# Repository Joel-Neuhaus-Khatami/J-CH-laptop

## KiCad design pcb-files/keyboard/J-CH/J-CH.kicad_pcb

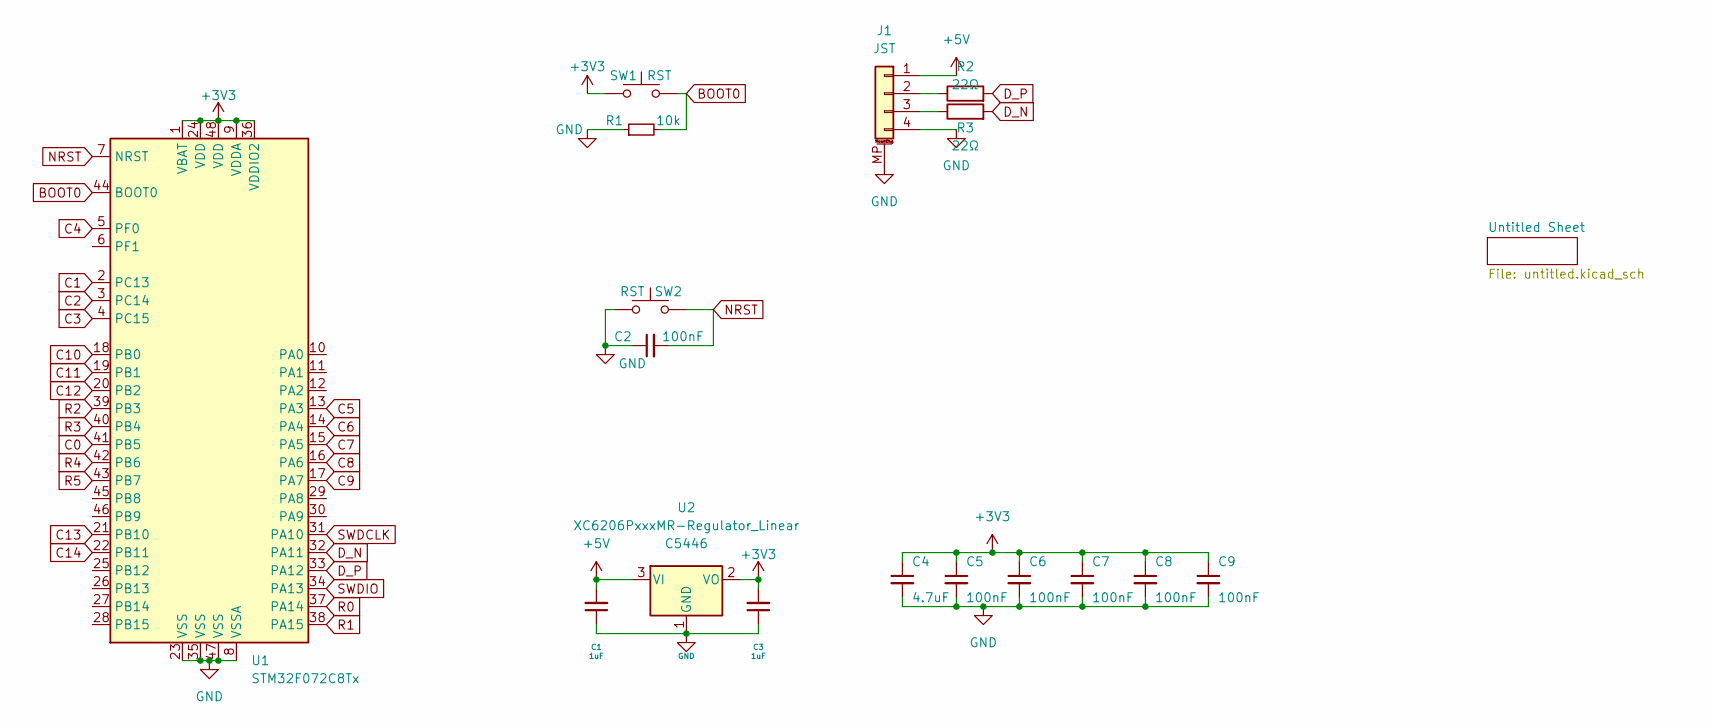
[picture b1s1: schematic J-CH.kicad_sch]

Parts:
C1, C3: 1uF; C_0402_1005Metric; LCSC C52923
C2, C5, C6, C7, C8, C9: 100nF; C_0402_1005Metric; LCSC C307331
C4: 4.7uF; C_0402_1005Metric; LCSC C23733
J1: JST; Molex_Pico-EZmate_78171-0004_1x04-1MP_P1.20mm_Vertical; LCSC C588524
R1: 10k; R_0402_1005Metric; LCSC C25744
R2, R3: 22Ω; C_0402_1005Metric; LCSC C25092
SW1, SW2: RST; SW_SPST_SKQG_WithoutStem; LCSC C139779
U1: STM32F072C8Tx; LQFP-48_7x7mm_P0.5mm; LCSC C80488
U2: XC6206PxxxMR-Regulator_Linear; SOT-23; LCSC C5446

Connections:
+3V3: C3.2, C4.1, C5.1, C6.1, C7.1, C8.1, C9.1, SW1.1, U1.1 (VBAT), U1.9 (VDDA), U1.24 (VDD), U1.36 (VDDIO2), U1.48 (VDD), U2.2 (VO)
+5V: C1.2, J1.1, U2.3 (VI)
BOOT0: R1.2, SW1.2, U1.44 (BOOT0)
C0: U1.41 (PB5); also elsewhere on the board
C1: U1.2 (PC13); also elsewhere on the board
C2: U1.3 (PC14); also elsewhere on the board
C3: U1.4 (PC15); also elsewhere on the board
C4: U1.5 (PF0); also elsewhere on the board
C5: U1.13 (PA3); also elsewhere on the board
C6: U1.14 (PA4); also elsewhere on the board
C7: U1.15 (PA5); also elsewhere on the board
C8: U1.16 (PA6); also elsewhere on the board
C9: U1.17 (PA7); also elsewhere on the board
C10: U1.18 (PB0); also elsewhere on the board
C11: U1.19 (PB1); also elsewhere on the board
C12: U1.20 (PB2); also elsewhere on the board
C13: U1.21 (PB10); also elsewhere on the board
C14: U1.22 (PB11); also elsewhere on the board
D_N: R2.2, U1.32 (PA11)
D_P: R3.2, U1.33 (PA12)
GND: C1.1, C2.1, C3.1, C4.2, C5.2, C6.2, C7.2, C8.2, C9.2, J1.4, J1.MP (MountPin), R1.1, SW2.2, U1.8 (VSSA), U1.23 (VSS), U1.35 (VSS), U1.47 (VSS), U2.1 (GND); also elsewhere on the board
NRST: C2.2, SW2.1, U1.7 (NRST); also elsewhere on the board
unnamed: J1.2, R3.1
unnamed: J1.3, R2.1
R0: U1.37 (PA14); also elsewhere on the board
R1: U1.38 (PA15); also elsewhere on the board
R2: U1.39 (PB3); also elsewhere on the board
R3: U1.40 (PB4); also elsewhere on the board
R4: U1.42 (PB6); also elsewhere on the board
R5: U1.43 (PB7); also elsewhere on the board
SWDCLK: U1.31 (PA10)
SWDIO: U1.34 (PA13)

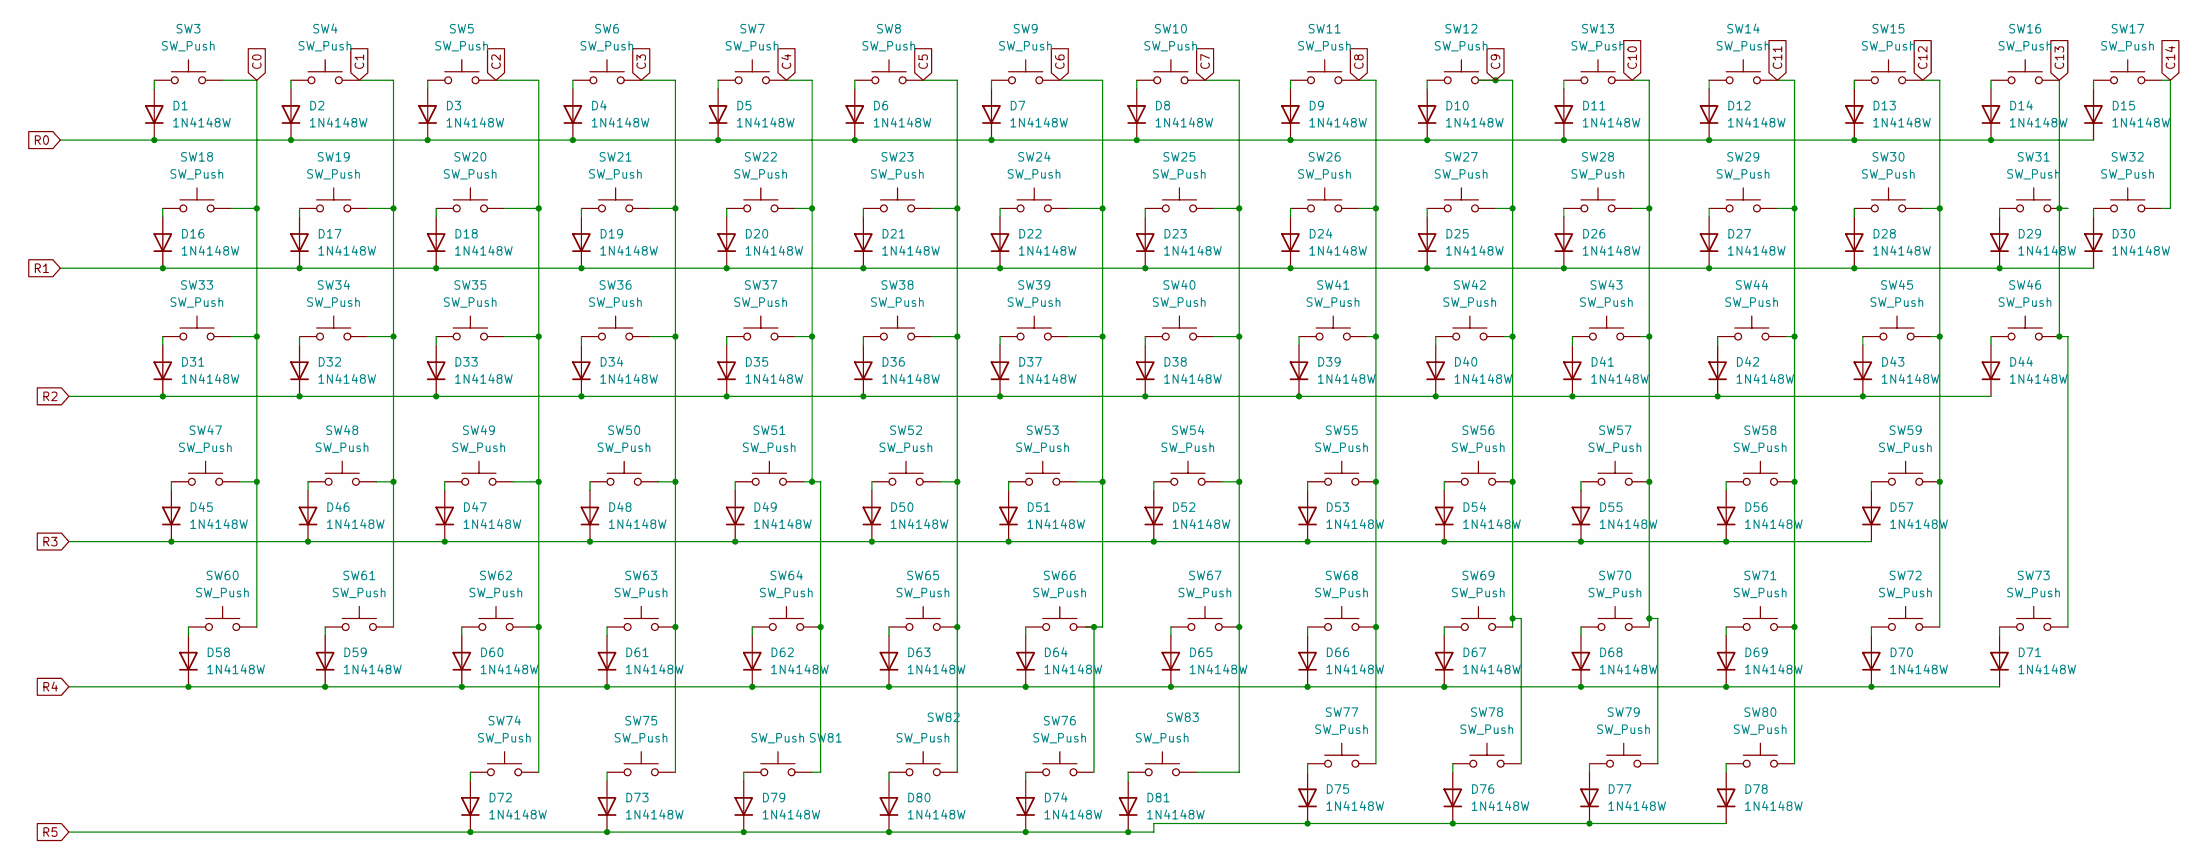
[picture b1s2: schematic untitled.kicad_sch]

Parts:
D1, D2, D3, D4, D5, D6, D7, D8, D9, D10, D11, D12, D13, D14, D15, D16, D17, D18, D19, D20, D21, D22, D23, D24, D25, D26, D27, D28, D29, D30, D31, D32, D33, D34, D35, D36, D37, D38, D39, D40, D41, D42, D43, D44, D45, D46, D47, D48, D49, D50, D51, D52, D53, D54, D55, D56, D57, D58, D59, D60, D61, D62, D63, D64, D65, D66, D67, D68, D69, D70, D71, D72, D73, D74, D75, D76, D77, D78, D79, D80, D81: 1N4148W; D_SOD-123
SW3, SW4, SW5, SW6, SW7, SW8, SW9, SW10, SW11, SW12, SW13, SW14, SW15, SW16, SW17, SW18, SW19, SW20, SW21, SW22, SW23, SW24, SW25, SW26, SW27, SW28, SW29, SW30, SW31, SW32, SW34, SW35, SW36, SW37, SW38, SW39, SW40, SW41, SW42, SW43, SW44, SW45, SW48, SW49, SW50, SW51, SW52, SW53, SW54, SW55, SW56, SW57, SW58, SW61, SW62, SW63, SW64, SW65, SW66, SW67, SW68, SW69, SW70, SW71, SW73, SW75, SW77, SW78, SW79, SW80, SW82: SW_Push; SW_Cherry_MX_1.00u_PCB
SW33, SW46, SW81, SW83: SW_Push; SW_Cherry_MX_1.50u_PCB
SW47, SW72: SW_Push; SW_Cherry_MX_1.75u_PCB
SW59: SW_Push; SW_Cherry_MX_2.25u_PCB
SW60, SW74: SW_Push; SW_Cherry_MX_1.25u_PCB
SW76: SW_Push; SW_Cherry_MX_6.25u_PCB

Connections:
C0: SW3.2, SW18.2, SW33.2, SW47.2, SW60.2; also elsewhere on the board
C1: SW4.2, SW19.2, SW34.2, SW48.2, SW61.2; also elsewhere on the board
C2: SW5.2, SW20.2, SW35.2, SW49.2, SW62.2, SW74.2; also elsewhere on the board
C3: SW6.2, SW21.2, SW36.2, SW50.2, SW63.2, SW75.2; also elsewhere on the board
C4: SW7.2, SW22.2, SW37.2, SW51.2, SW64.2, SW81.2; also elsewhere on the board
C5: SW8.2, SW23.2, SW38.2, SW52.2, SW65.2, SW82.2; also elsewhere on the board
C6: SW9.2, SW24.2, SW39.2, SW53.2, SW66.2, SW76.2; also elsewhere on the board
C7: SW10.2, SW25.2, SW40.2, SW54.2, SW67.2, SW83.2; also elsewhere on the board
C8: SW11.2, SW26.2, SW41.2, SW55.2, SW68.2, SW77.2; also elsewhere on the board
C9: SW12.2, SW27.2, SW42.2, SW56.2, SW69.2, SW78.2; also elsewhere on the board
C10: SW13.2, SW28.2, SW43.2, SW57.2, SW70.2, SW79.2; also elsewhere on the board
C11: SW14.2, SW29.2, SW44.2, SW58.2, SW71.2, SW80.2; also elsewhere on the board
C12: SW15.2, SW30.2, SW45.2, SW59.1, SW72.2; also elsewhere on the board
C13: SW16.2, SW31.2, SW46.2, SW73.2; also elsewhere on the board
C14: SW17.2, SW32.2; also elsewhere on the board
unnamed: D1.2 (A), SW3.1
unnamed: D2.2 (A), SW4.1
unnamed: D3.2 (A), SW5.1
unnamed: D4.2 (A), SW6.1
unnamed: D5.2 (A), SW7.1
unnamed: D6.2 (A), SW8.1
unnamed: D7.2 (A), SW9.1
unnamed: D8.2 (A), SW10.1
unnamed: D9.2 (A), SW11.1
unnamed: D10.2 (A), SW12.1
unnamed: D11.2 (A), SW13.1
unnamed: D12.2 (A), SW14.1
unnamed: D13.2 (A), SW15.1
unnamed: D14.2 (A), SW16.1
unnamed: D15.2 (A), SW17.1
unnamed: D16.2 (A), SW18.1
unnamed: D17.2 (A), SW19.1
unnamed: D18.2 (A), SW20.1
unnamed: D19.2 (A), SW21.1
unnamed: D20.2 (A), SW22.1
unnamed: D21.2 (A), SW23.1
unnamed: D22.2 (A), SW24.1
unnamed: D23.2 (A), SW25.1
unnamed: D24.2 (A), SW26.1
unnamed: D25.2 (A), SW27.1
unnamed: D26.2 (A), SW28.1
unnamed: D27.2 (A), SW29.1
unnamed: D28.2 (A), SW30.1
unnamed: D29.2 (A), SW31.1
unnamed: D30.2 (A), SW32.1
unnamed: D31.2 (A), SW33.1
unnamed: D32.2 (A), SW34.1
unnamed: D33.2 (A), SW35.1
unnamed: D34.2 (A), SW36.1
unnamed: D35.2 (A), SW37.1
unnamed: D36.2 (A), SW38.1
unnamed: D37.2 (A), SW39.1
unnamed: D38.2 (A), SW40.1
unnamed: D39.2 (A), SW41.1
unnamed: D40.2 (A), SW42.1
unnamed: D41.2 (A), SW43.1
unnamed: D42.2 (A), SW44.1
unnamed: D43.2 (A), SW45.1
unnamed: D44.2 (A), SW46.1
unnamed: D45.2 (A), SW47.1
unnamed: D46.2 (A), SW48.1
unnamed: D47.2 (A), SW49.1
unnamed: D48.2 (A), SW50.1
unnamed: D49.2 (A), SW51.1
unnamed: D50.2 (A), SW52.1
unnamed: D51.2 (A), SW53.1
unnamed: D52.2 (A), SW54.1
unnamed: D53.2 (A), SW55.1
unnamed: D54.2 (A), SW56.1
unnamed: D55.2 (A), SW57.1
unnamed: D56.2 (A), SW58.1
unnamed: D57.2 (A), SW59.2
unnamed: D58.2 (A), SW60.1
unnamed: D59.2 (A), SW61.1
unnamed: D60.2 (A), SW62.1
unnamed: D61.2 (A), SW63.1
unnamed: D62.2 (A), SW64.1
unnamed: D63.2 (A), SW65.1
unnamed: D64.2 (A), SW66.1
unnamed: D65.2 (A), SW67.1
unnamed: D66.2 (A), SW68.1
unnamed: D67.2 (A), SW69.1
unnamed: D68.2 (A), SW70.1
unnamed: D69.2 (A), SW71.1
unnamed: D70.2 (A), SW72.1
unnamed: D71.2 (A), SW73.1
unnamed: D72.2 (A), SW74.1
unnamed: D73.2 (A), SW75.1
unnamed: D74.2 (A), SW76.1
unnamed: D75.2 (A), SW77.1
unnamed: D76.2 (A), SW78.1
unnamed: D77.2 (A), SW79.1
unnamed: D78.2 (A), SW80.1
unnamed: D79.2 (A), SW81.1
unnamed: D80.2 (A), SW82.1
unnamed: D81.2 (A), SW83.1
R0: D1.1 (K), D2.1 (K), D3.1 (K), D4.1 (K), D5.1 (K), D6.1 (K), D7.1 (K), D8.1 (K), D9.1 (K), D10.1 (K), D11.1 (K), D12.1 (K), D13.1 (K), D14.1 (K), D15.1 (K); also elsewhere on the board
R1: D16.1 (K), D17.1 (K), D18.1 (K), D19.1 (K), D20.1 (K), D21.1 (K), D22.1 (K), D23.1 (K), D24.1 (K), D25.1 (K), D26.1 (K), D27.1 (K), D28.1 (K), D29.1 (K), D30.1 (K); also elsewhere on the board
R2: D31.1 (K), D32.1 (K), D33.1 (K), D34.1 (K), D35.1 (K), D36.1 (K), D37.1 (K), D38.1 (K), D39.1 (K), D40.1 (K), D41.1 (K), D42.1 (K), D43.1 (K), D44.1 (K); also elsewhere on the board
R3: D45.1 (K), D46.1 (K), D47.1 (K), D48.1 (K), D49.1 (K), D50.1 (K), D51.1 (K), D52.1 (K), D53.1 (K), D54.1 (K), D55.1 (K), D56.1 (K), D57.1 (K); also elsewhere on the board
R4: D58.1 (K), D59.1 (K), D60.1 (K), D61.1 (K), D62.1 (K), D63.1 (K), D64.1 (K), D65.1 (K), D66.1 (K), D67.1 (K), D68.1 (K), D69.1 (K), D70.1 (K), D71.1 (K); also elsewhere on the board
R5: D72.1 (K), D73.1 (K), D74.1 (K), D75.1 (K), D76.1 (K), D77.1 (K), D78.1 (K), D79.1 (K), D80.1 (K), D81.1 (K); also elsewhere on the board

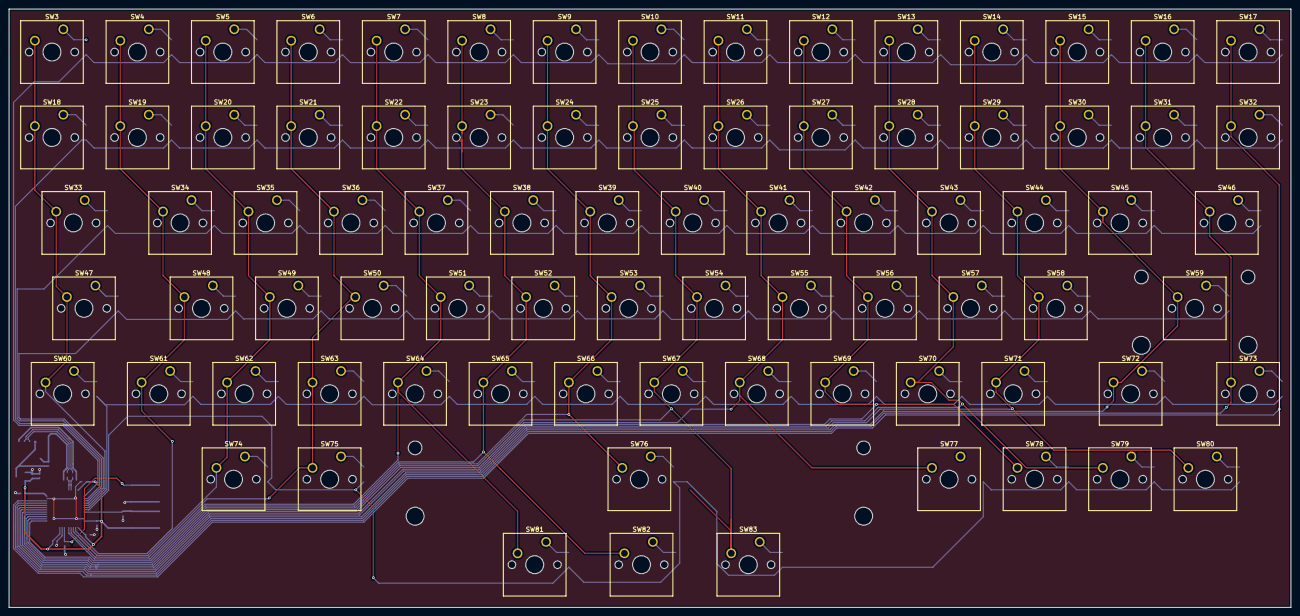
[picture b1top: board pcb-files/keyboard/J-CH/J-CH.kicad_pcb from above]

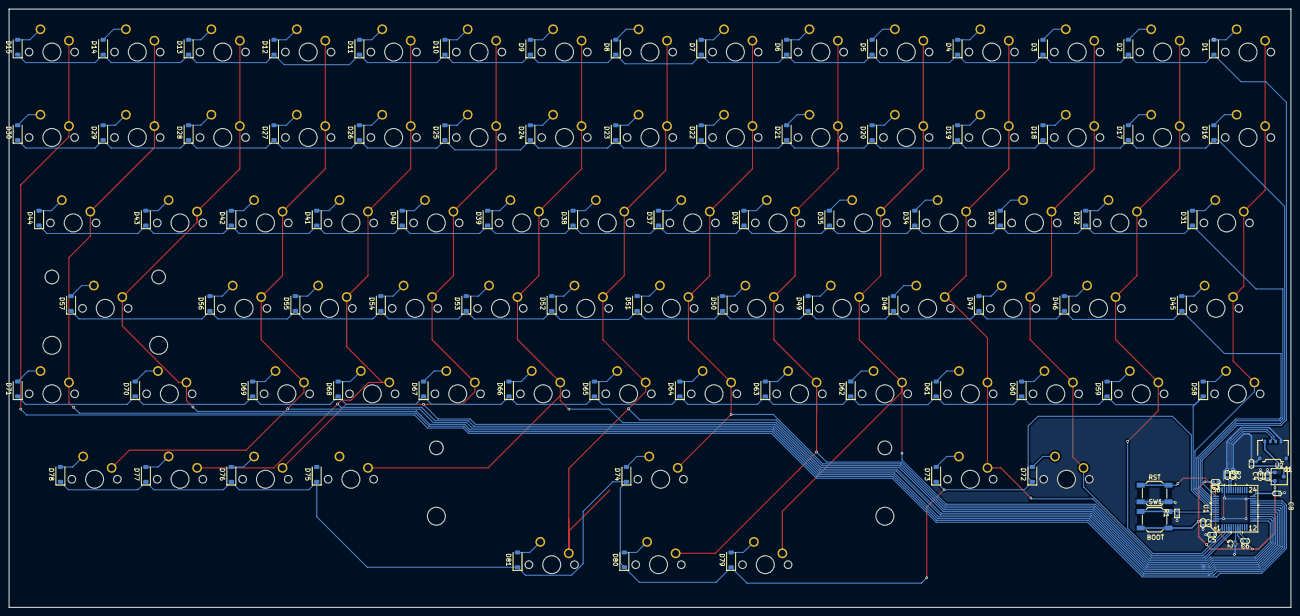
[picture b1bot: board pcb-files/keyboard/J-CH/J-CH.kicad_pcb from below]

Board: 2 copper layers, 285.8 x 133.4 mm, 179 parts (98 on the bottom side), 111 nets.

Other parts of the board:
RST: RST; SW_SPST_SKQG_WithoutStem

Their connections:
GND: RST.2; also elsewhere on the board
NRST: RST.1; also elsewhere on the board

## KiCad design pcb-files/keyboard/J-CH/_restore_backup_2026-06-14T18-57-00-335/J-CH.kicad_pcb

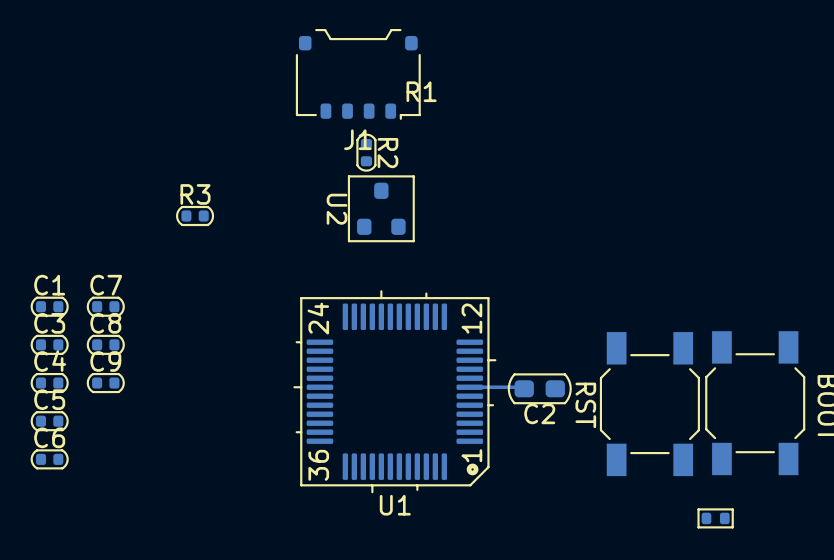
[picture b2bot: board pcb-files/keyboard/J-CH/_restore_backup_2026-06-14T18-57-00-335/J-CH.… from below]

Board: 2 copper layers, 17 parts (17 on the bottom side), 9 nets.

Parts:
BOOT: RST; SW_SPST_SKQG_WithoutStem
C1, C3: 1uF; C_0402_1005Metric
C2: 100nF; C_0603_1608Metric_Pad1.08x0.95mm
C4: 4.7uF; C_0402_1005Metric
C5, C6, C7, C8, C9: 100nF; C_0402_1005Metric
J1: JST; Molex_Pico-EZmate_78171-0004_1x04-1MP_P1.20mm_Vertical
R1: 10k; R_0402_1005Metric
R2, R3: 22Ω; C_0402_1005Metric
RST: RST; SW_SPST_SKQG_WithoutStem
U1: STM32F072C8Tx; LQFP-48_7x7mm_P0.5mm
U2: XC6206PxxxMR-Regulator_Linear; SOT-23

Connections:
+3V3: BOOT.1, C3.2, C4.1, C5.1, C6.1, C7.1, C8.1, C9.1, U2.2 (VO)
+5V: C1.2, J1.1, U2.3 (VI)
BOOT0: BOOT.2, R1.2, U1.44 (BOOT0)
D_N: R2.2, U1.32 (PA11)
D_P: R3.2, U1.33 (PA12)
GND: C1.1, C2.1, C3.1, C4.2, C5.2, C6.2, C7.2, C8.2, C9.2, J1.4, J1.MP (MountPin), R1.1, RST.1, U2.1 (GND)
NRST: C2.2, RST.2, U1.7 (NRST)
unnamed: J1.2, R2.1
unnamed: J1.3, R3.1

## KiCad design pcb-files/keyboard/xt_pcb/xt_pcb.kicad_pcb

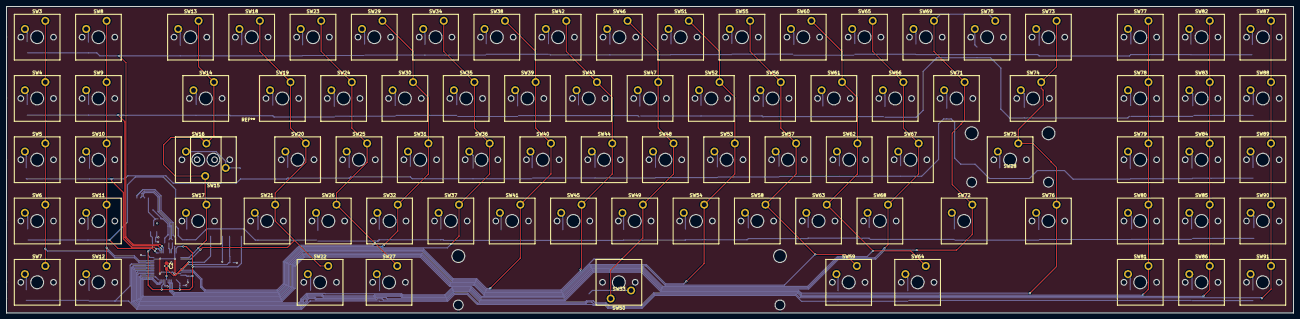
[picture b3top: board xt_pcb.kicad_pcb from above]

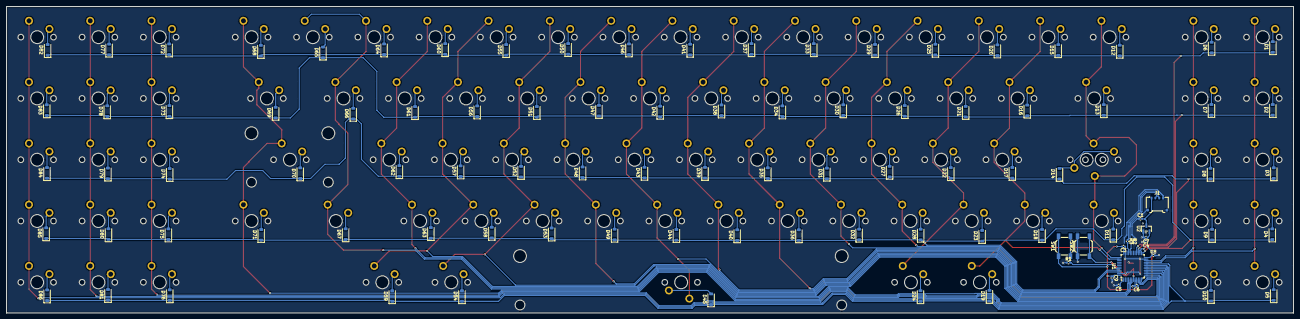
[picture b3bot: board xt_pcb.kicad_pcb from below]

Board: 2 copper layers, 400.1 x 95.2 mm, 192 parts (102 on the bottom side), 119 nets.

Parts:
C1, C3: 1uF; C_0402_1005Metric
C2: 100nF; C_0603_1608Metric_Pad1.08x0.95mm_HandSolder
C4: 4.7uF; C_0402_1005Metric
C5, C6, C7, C8, C9: 100nF; C_0402_1005Metric
D1, D2, D3, D4, D5, D6, D7, D8, D9, D10, D11, D12, D13, D14, D15, D16, D17, D18, D19, D20, D21, D22, D23, D24, D25, D26, D27, D28, D29, D30, D31, D32, D33, D34, D35, D36, D37, D38, D39, D40, D41, D42, D43, D44, D45, D46, D47, D48, D49, D50, D51, D52, D53, D54, D55, D56, D57, D58, D59, D60, D61, D62, D63, D64, D65, D66, D67, D68, D69, D70, D71, D72, D73, D74, D75, D76, D77, D78, D79, D80, D81, D82, D83, D84, D85, D86: D; D_SOD-123
J1: JST; Molex_Pico-EZmate_78171-0004_1x04-1MP_P1.20mm_Vertical
R1: 10k; R_0402_1005Metric
R2, R3: 22Ω; C_0402_1005Metric
SW1, SW2: RST; SW_SPST_SKQG_WithoutStem
SW3, SW4, SW5, SW6, SW7, SW8, SW9, SW10, SW11, SW12, SW13, SW18, SW19, SW20, SW21, SW22, SW23, SW24, SW25, SW26, SW29, SW30, SW31, SW32, SW34, SW35, SW36, SW37, SW38, SW39, SW40, SW41, SW42, SW43, SW44, SW45, SW46, SW47, SW48, SW49, SW51, SW52, SW53, SW54, SW55, SW56, SW57, SW58, SW60, SW61, SW62, SW63, SW64, SW65, SW66, SW67, SW68, SW69, SW70, SW71, SW73, SW76, SW77, SW78, SW79, SW80, SW81, SW82, SW83, SW84, SW85, SW86, SW87, SW88, SW89, SW90, SW91: SW_Push; SW_Cherry_MX_PCB_1.00u
SW14, SW74: SW_Push; SW_Cherry_MX_PCB_1.50u
SW15: SW_Push; SW_Cherry_MX_PCB_1.75u
SW16, SW17, SW27, SW59: SW_Push; SW_Cherry_MX_PCB_1.25u
SW28: SW_Push; Stabilizer_Cherry_MX_2.00u
SW33: SW_Push; Stabilizer_Cherry_MX_6.25u
SW50: SW_Push; SW_Cherry_MX_PCB_6.25u
SW72: SW_Push; SW_Cherry_MX_Plate_1.75u
SW75: SW_Push; SW_Cherry_MX_PCB_2.25u
U1: STM32F072C8Tx; LQFP-48_7x7mm_P0.5mm
U2: XC6206PxxxMR-Regulator_Linear; SOT-23

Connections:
+3V3: C3.2, C4.1, C5.1, C6.1, C7.1, C8.1, C9.1, SW1.1, U1.1 (VBAT), U1.9 (VDDA), U1.24 (VDD), U1.36 (VDDIO2), U1.48 (VDD), U2.2 (VO)
+5V: C1.2, J1.1, U2.3 (VI)
BOOT0: R1.2, SW1.2, U1.44 (BOOT0)
C1: SW3.2, SW4.2, SW5.2, SW6.2, SW7.2, U1.21 (PB10)
C2: SW8.2, SW9.2, SW10.2, SW11.2, SW12.2, U1.22 (PB11)
C3: SW13.2, SW14.2, SW15.2, SW16.2, SW17.2, U1.37 (PA14)
C4: SW18.2, SW19.2, SW20.2, SW21.2, SW22.2, U1.38 (PA15)
C5: SW23.2, SW24.2, SW25.2, SW26.2, SW27.2, U1.45 (PB8)
C6: SW29.2, SW30.2, SW31.2, SW32.2, U1.46 (PB9)
C7: SW34.2, SW35.2, SW36.2, SW37.2, U1.4 (PC15)
C8: SW38.2, SW39.2, SW40.2, SW41.2, U1.5 (PF0)
C9: SW42.2, SW43.2, SW44.2, SW45.2, U1.6 (PF1)
C10: SW46.2, SW47.2, SW48.2, SW49.2, SW50.2, U1.10 (PA0)
C11: SW51.2, SW52.2, SW53.2, SW54.2, U1.11 (PA1)
C12: SW55.2, SW56.2, SW57.2, SW58.2, SW59.2, U1.12 (PA2)
C13: SW60.2, SW61.2, SW62.2, SW63.2, SW64.2, U1.13 (PA3)
C14: SW65.2, SW66.2, SW67.2, SW68.2, U1.14 (PA4)
C15: SW69.2, SW70.2, SW71.2, SW72.2, U1.15 (PA5)
C16: SW73.2, SW74.2, SW75.2, SW76.2, U1.16 (PA6)
C17: SW77.2, SW78.2, SW79.2, SW80.2, SW81.2, U1.17 (PA7)
C18: SW82.2, SW83.2, SW84.2, SW85.2, SW86.2, U1.18 (PB0)
C19: SW87.2, SW88.2, SW89.2, SW90.2, SW91.2, U1.19 (PB1)
D_N: R2.2, U1.32 (PA11)
D_P: R3.2, U1.33 (PA12)
GND: C1.1, C2.1, C3.1, C4.2, C5.2, C6.2, C7.2, C8.2, C9.2, J1.4, J1.MP (MountPin), R1.1, SW2.1, U1.8 (VSSA), U1.23 (VSS), U1.35 (VSS), U1.47 (VSS), U2.1 (GND)
NRST: C2.2, SW2.2, U1.7 (NRST)
unnamed: D1.2 (A), SW3.1
unnamed: D2.2 (A), SW4.1
unnamed: D3.2 (A), SW5.1
unnamed: D4.2 (A), SW6.1
unnamed: D5.2 (A), SW7.1
unnamed: D6.2 (A), SW8.1
unnamed: D7.2 (A), SW9.1
unnamed: D8.2 (A), SW10.1
unnamed: D9.2 (A), SW11.1
unnamed: D10.2 (A), SW12.1
unnamed: D11.2 (A), SW17.1
unnamed: D12.2 (A), SW13.1
unnamed: D13.2 (A), SW14.1
unnamed: D14.2 (A), SW15.1, SW16.1
unnamed: D15.2 (A), SW18.1
unnamed: D16.2 (A), SW19.1
unnamed: D17.2 (A), SW20.1
unnamed: D18.2 (A), SW21.1
unnamed: D19.2 (A), SW22.1
unnamed: D20.2 (A), SW23.1
unnamed: D21.2 (A), SW24.1
unnamed: D22.2 (A), SW25.1
unnamed: D23.2 (A), SW26.1
unnamed: D24.2 (A), SW27.1
unnamed: D25.2 (A), SW29.1
unnamed: D26.2 (A), SW30.1
unnamed: D27.2 (A), SW31.1
unnamed: D28.2 (A), SW32.1
unnamed: D29.2 (A), SW34.1
unnamed: D30.2 (A), SW35.1
unnamed: D31.2 (A), SW36.1
unnamed: D32.2 (A), SW37.1
unnamed: D33.2 (A), SW38.1
unnamed: D34.2 (A), SW39.1
unnamed: D35.2 (A), SW40.1
unnamed: D36.2 (A), SW41.1
unnamed: D37.2 (A), SW42.1
unnamed: D38.2 (A), SW43.1
unnamed: D39.2 (A), SW44.1
unnamed: D40.2 (A), SW45.1
unnamed: D41.2 (A), SW46.1
unnamed: D42.2 (A), SW47.1
unnamed: D43.2 (A), SW48.1
unnamed: D44.2 (A), SW49.1
unnamed: D45.2 (A), SW50.1
unnamed: D46.2 (A), SW51.1
unnamed: D47.2 (A), SW52.1
unnamed: D48.2 (A), SW53.1
unnamed: D49.2 (A), SW54.1
unnamed: D50.2 (A), SW55.1
unnamed: D51.2 (A), SW56.1
unnamed: D52.2 (A), SW57.1
unnamed: D53.2 (A), SW58.1
unnamed: D54.2 (A), SW59.1
unnamed: D55.2 (A), SW60.1
unnamed: D56.2 (A), SW61.1
unnamed: D57.2 (A), SW62.1
unnamed: D58.2 (A), SW63.1
unnamed: D59.2 (A), SW64.1
unnamed: D60.2 (A), SW65.1
unnamed: D61.2 (A), SW66.1
unnamed: D62.2 (A), SW67.1
unnamed: D63.2 (A), SW68.1
unnamed: D64.2 (A), SW69.1
unnamed: D65.2 (A), SW70.1
unnamed: D66.2 (A), SW71.1
unnamed: D67.2 (A), SW72.1
unnamed: D68.2 (A), SW73.1
unnamed: D69.2 (A), SW74.1
unnamed: D70.2 (A), SW75.1
unnamed: D71.2 (A), SW76.1
unnamed: D72.2 (A), SW77.1
unnamed: D73.2 (A), SW78.1
unnamed: D74.2 (A), SW79.1
unnamed: D75.2 (A), SW80.1
unnamed: D76.2 (A), SW81.1
unnamed: D77.2 (A), SW82.1
unnamed: D78.2 (A), SW83.1
unnamed: D79.2 (A), SW84.1
unnamed: D80.2 (A), SW85.1
unnamed: D81.2 (A), SW86.1
unnamed: D82.2 (A), SW87.1
unnamed: D83.2 (A), SW88.1
unnamed: D84.2 (A), SW89.1
unnamed: D85.2 (A), SW90.1
unnamed: D86.2 (A), SW91.1
unnamed: J1.2, R2.1
unnamed: J1.3, R3.1
R1: D1.1 (K), D6.1 (K), D12.1 (K), D15.1 (K), D20.1 (K), D25.1 (K), D29.1 (K), D33.1 (K), D37.1 (K), D41.1 (K), D46.1 (K), D50.1 (K), D55.1 (K), D60.1 (K), D64.1 (K), D68.1 (K), D72.1 (K), D77.1 (K), D82.1 (K), U1.28 (PB15)
R2: D2.1 (K), D7.1 (K), D13.1 (K), D16.1 (K), D21.1 (K), D26.1 (K), D30.1 (K), D34.1 (K), D38.1 (K), D42.1 (K), D47.1 (K), D51.1 (K), D56.1 (K), D61.1 (K), D65.1 (K), D69.1 (K), D73.1 (K), D78.1 (K), D83.1 (K), U1.27 (PB14)
R3: D3.1 (K), D8.1 (K), D14.1 (K), D17.1 (K), D22.1 (K), D27.1 (K), D31.1 (K), D35.1 (K), D39.1 (K), D43.1 (K), D48.1 (K), D52.1 (K), D57.1 (K), D62.1 (K), D66.1 (K), D70.1 (K), D74.1 (K), D79.1 (K), D84.1 (K), U1.26 (PB13)
R4: D4.1 (K), D9.1 (K), D11.1 (K), D18.1 (K), D23.1 (K), D28.1 (K), D32.1 (K), D36.1 (K), D40.1 (K), D44.1 (K), D49.1 (K), D53.1 (K), D58.1 (K), D63.1 (K), D67.1 (K), D71.1 (K), D75.1 (K), D80.1 (K), D85.1 (K), U1.25 (PB12)
R5: D5.1 (K), D10.1 (K), D19.1 (K), D24.1 (K), D45.1 (K), D54.1 (K), D59.1 (K), D76.1 (K), D81.1 (K), D86.1 (K), U1.20 (PB2)

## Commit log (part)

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2026-06-07 init commit
2026-06-22 keyboard designed
